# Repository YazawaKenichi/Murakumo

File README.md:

# Murakumo

```
* 8b    d8 88   88 88""Yb    db    88  dP 88   88 8b    d8  dP"Yb             Yb    dP 888888 *
* 88b  d88 88   88 88__dP   dPYb   88odP  88   88 88b  d88 dP   Yb             Yb  dP  88oo." *
* 88YbdP88 Y8   8P 88"Yb   dP__Yb  88"Yb  Y8   8P 88YbdP88 Yb   dP              YbdP      `8b *
* 88 YY 88 `YbodP' 88  Yb dP""""Yb 88  Yb `YbodP' 88 YY 88  YbodP  oooooooooo    YP    8888P' *
```

Yazawa の初めてのロボトレの情報を置いておくリポジトリ。
##### Excel フォルダ
機体の仕様決定

##### Inventor フォルダ
具体的な機体のグラフィック

##### Circuit フォルダ
KiCAD データとガーバーデータ

##### Program フォルダ（未作成）
実行プログラムや試行錯誤したプログラム

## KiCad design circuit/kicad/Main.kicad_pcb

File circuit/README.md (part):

回路設計時のノート

いろいろ悩みそうなところだけど、どこから悩めばいいのかもわからなかったので、まずはモータドライバ回路から設計しようと思う。

モータドライバ設計の前に、H ブリッジを駆動するためのゲートドライバ選びについて記述する。
##### ゲートドライバ
まず、ゲートドライバに必要な要素は以下の通り。
- Nch フルブリッジ回路を組むことができるか？
- 100% duty で出力できるか？
ということらしい。

PWM 周波数の話。
PWM 周波数は小さすぎるとトルクが足りなくなり、大きすぎるとモータによるサージの影響を受けやすくなる。よって適度な周波数に決める必要がある。

###### Nch フルブリッジ回路
Nch フルブリッジ回路を組むことの利点は以下。
- Pch は Nch に比べて性能が低い。
- Pch は品種があまりない。
- パワー素子は一種類のみで済ませて手間を省きたい。（Pch か Nch にそろえて同じ素子を使って製作できるようにしたい。）
- Pch は値段が高い。
上記理由を先輩に教えていただいたが、教えていただいた後にネットを探したところ、同様の記述を発見した。[参考](http://blog.livedoor.jp/wata_net/archives/2147292.html)。
[こっちのサイト](https://qiita.com/panzakii/items/97eca16954d34ecf0c8b)には「なぜフルNchにこだわるかというと、単純にその方が流せる電流が大きくなるからです。実はPchFETはNchFETに比べ流せる電流が少ないのです。原理について説明しだすと本当にキリがないので説明しません。興味のある人はググってください。」などと記述されているが、ググってもそんな記述は一切出てこない。なんなんだ。

「品種が多いから Pch よりも大電流の流せる Nch MOSFET」ならわかるが、「原理」とか「説明しだすとキリがない」とか記述されているのは本当に意味が分からない。

###### 100% duty で出力
- 最大出力で出せたほうが良いにきまっとるやろ！

二つのメリットをカバーできて、より入手しやすい IC が A3921 だそうで、それが理由でよく利用される。

##### モータドライバ
ゲートドライバが決まったところで、次に使用する FET とそれにつながる制限抵抗やコンデンサの値を決める必要がある。
特にこの抵抗とコンデンサは真剣に決めないとショートしてリポが死ぬ。マジで。
モータに入る電流は最大でも 4.34A なので、この許容電流に耐えうるケーブルは AWG22 になる。（AWG23 がいい感じに 4.7A の許容電流なのだが、9号館にないのでしょうがない。）
この AWG23 を圧着できるコネクタが XA コネクタなので、モータの電流が通るところのコネクタはすべて XA にしようと思う。
電源コネクタと電源回路をモータドライバ回路の方に設置することで、わざわざマイコン側から電力をモータドライバ回路に送る必要を無くす。

***書き途中***

DRV8874 のデータシートを読んで得た情報
- CPH CPL 間に 22nF のコンデンサ
- nFault は故障で LOW nSleep は LOW でスリープ => nFault と nSleep を直結すると故障と同時にスリープに入る。
- nFault には外部プルアップが必要。

SR ピンは 1 にすると FET 経由で回生する

SR ピンを 0 にするとダイオード経由で回生する

Figure 2: Fast Decay Power Bridge Current Paths が一番創造に近いモータドライバの制御に近い

PWMH PWML には常に 1 を入れて、PHASE に 

##### CPU
先輩が STM32F405RGT6 を束買いしているので、とりあえずこれにするのはアリ。
クロック数とメモリと機能的に、ロボトレにいい塩梅で使えそうなのがこの CPU らしい。

***書き途中***

##### 電源回路
この電源回路を決めるのにレギュレータを選ぶ必要があるのだが、レギュレータの出力が決まらない以上は手の付けようがない。だからさっさとほかの回路作れ。電源選びは最後だ。
=======
回路設計時のノート

いろいろ悩みそうなところだけど、どこから悩めばいいのかもわからなかったので、まずはモータドライバ回路から設計しようと思う。

使いたいモータがある -> 必要な電流量に耐える FET -> それを駆動できるゲートドライバを探す<br>
使いたいセンサがある -> 

モータドライバ設計の前に、H ブリッジを駆動するためのゲートドライバ選びについて記述する。
##### ゲートドライバ
まず、ゲートドライバに必要な要素は以下の通り。
- Nch フルブリッジ回路を組むことができるか？
- 100% duty で出力できるか？
ということらしい。

###### Nch フルブリッジ回路
Nch フルブリッジ回路を組むことの利点は以下。
- Pch は Nch に比べて性能が低い。
- Pch は品種があまりない。
- パワー素子は一種類のみで済ませて手間を省きたい。（Pch か Nch にそろえて同じ素子を使って製作できるようにしたい。）
- Pch は値段が高い。
上記理由を先輩に教えていただいたが、教えていただいた後にネットを探したところ、同様の記述を発見した。[参考](http://blog.livedoor.jp/wata_net/archives/2147292.html)。
[こっちのサイト](https://qiita.com/panzakii/items/97eca16954d34ecf0c8b)には「なぜフルNchにこだわるかというと、単純にその方が流せる電流が大きくなるからです。実はPchFETはNchFETに比べ流せる電流が少ないのです。原理について説明しだすと本当にキリがないので説明しません。興味のある人はググってください。」などと記述されているが、ググってもそんな記述は一切出てこない。なんなんだ。

「品種が多いから Pch よりも大電流の流せる Nch MOSFET」ならわかるが、「原理」とか「説明しだすとキリがない」とか記述されているのは本当に意味が分からない。

###### 100% duty で出力
- 最大出力で出せたほうが良いにきまっとるやろ！
100% duty で出せるかどうかってどうやって決まるんだろう...

二つのメリットをカバーできて、より入手しやすい IC が A3921 だそうで、それが理由でよく利用される。
A3921 の仕様
ゲート電圧は基準電位から +15V 以内の範囲が出力される様子。具体的には、ハイサイド出力が SA の電位よりも 0 ~ 15V 高くなり、ローサイド出力が GND 電位よりも -5 ~ 16V 高くなるように出力される。

A3921 のデータシートを読んで得た情報
- GHA and GHB Pins
- ゲート抵抗はできるだけ FET に近いところに置く必要がある。（なんでや）
- ＞ そもそもゲート抵抗をつける理由として
- ＞＞ FET 内部のコンデンサ成分と、導線自体によるインダクタンス成分が共振し、それに影響して FET やマイコンが破損する恐れがある。
- ＞＞ ドレイン電圧の立ち上がりと立下りが早すぎてノイズへの影響が大きくなる。
- ＞＞ ゲート電流が大きすぎて FET 前段の制御回路が破損する。
- ＞ この中で FET と抵抗の距離と関係がありそうな理由としては「導線自体のインダクタンス」だろう。抵抗からFETまでの導線の長さを小さくする、すなわちインダクタンスを小さくすることでノイズを軽減するといったところか。
- いまいちよくわからないところが、「GHx going low turns on the lower half of the drive, sinking current from the external FET gate circuit to the corresponding Sx pin, turning off the FET.」の一文で、GHx を Low にしたらドライブの下半分が ON になる？ってどういうことだ？
- Bootstrap Capacitor Selection
- ブートストラップコンデンサ CBOOTx は、正しく選択する必要がある。
- コンデンサの静電容量が大きいと、コンデンサの充電に時間が浪費され、結果として最大デューティーサイクルと PWM 周波数の制限が小さくなってしまう。
- 逆に小さいと、Charge Sharing によって、電荷が CBOOTx から FET ゲートに転送されるときに大きな電圧降下が発生する可能性があるらしい。
- ＞ Charge Sharing ってなんだ？
- ＞＞ 英語版 Wiki によると、Charge Sharing は、ある電子ドメインからほかの電子ドメインへの電荷の移動による信号劣化の影響。らしい。は？
- ＞ よくわからないけど、とにかく電荷を共有して、出力電圧レベルが退化したり、誤った出力値が発生したりする可能性があるっぽい。
- この電圧降下を小さくするために、CBOOTx の電荷 QBOOT は、FET のゲート QGATE に必要な電荷よりもはるかに大きくする必要がある。その"はるかに大きい"というのは、20 倍だそうだ。
- QBOOT というのは、CBOOTx に蓄えられる電気量なので、CBOOT * VBOOT で求めることができる。そして上記より、これは QGATE の 20 である必要があるので、ブートストラップに接続するコンデンサの、適切な電気容量 CBOOT を求める式は、以下のようになる。
- CBOOT = QGATE * 20 / VBOOT
- 係数 20 を選択した場合、FET が ON の時の VBOOT と OFF の時の VBOOT の差は約 5% だそう。通常動作条件下での VBOOT の最大電圧は VREG らしい。
- ＞ VREG の値について。。。疑問がある。
- ＞＞ Terminal List には Regulated 13V と説明があるのに、
- VBB 電源が 16V より大きいとき、レギュレータは単純なリニアレギュレータとなる。16V 未満では、安定したレギュレートをするために、ポンプコンデンサ CP が必要。
- このコンデンサ CP の最小値は 220nF である必要があり、通常は 470nF を接続する。
- 安定してレギュレートされた 13V は VREG 端子で使用できる。ローサイドドライブとブートストラップコンデンサに過渡充電電流を供給するために十分大きなストレージコンデンサを接続する必要がある。
参考になったサイト
- ハイサイド Nch MOSFET の話やブートストラップ回りについては[このサイト](https://techweb.rohm.co.jp/knowledge/dcdc/dcdc_sr/dcdc_sr01/829)が参考になった。

###### duty rate
[このサイト](https://sgrsn1711.hatenablog.com/entry/2019/04/29/152425)が参考になった。<br>
PWM 制御は PWM パルス波を用いて電圧を制御する方法。しかし **『PWM のデューティー比を線形に動かしても電圧は線形』にならない。** <br>
具体的な式は (実効値) = (最大瞬時値) * √(デューティー比)<br>
最大瞬時値：パルス波が HIGH の時の電圧<br>
デューティー比：そのままの意味（但し 0 以上 1 以下）<br>
実効値：PWM の電圧・電流をこれと同じ働きをする直流の電圧・電流の大きさに置き換えて表した値<br>
両辺を二乗して両辺を (モータの抵抗) で割ると<br>
(実効電圧) / (モータの抵抗) = (デューティー比) * (最大瞬時電圧) / (モータの抵抗)<br>
すなわち<br>
(実効電力) = (デューティー比) * (ドライバの電力)<br>
となり、**(デューティー比) は 電力 の比例定数となっている**ことがわかる。<br>
<br>
[このサイト](https://detail-infomation.com/gate-driver-type/)によると、ターンオンを速くする回路よりもターンオフを速くする回路の方が頻繁に用いられるらしい。たしかに、4月に制作したミニトレーサ回路も、ターンオフが速くなる方向にダイオードが設けられていた。ターンオフ抵抗が小さいので、MOSFET のミラー容量を介して誤ターンオンを防ぐことができるようだ。

##### モータドライバ
ゲートドライバが決まったところで、次に使用する FET とそれにつながる制限抵抗やコンデンサの値を決める必要がある。
特にこの抵抗とコンデンサは真剣に決めないとショートしてリポが死ぬ。マジで。

参考までに先輩のデータを置いておく。
DRV8874 (野村先輩)
DRV8873 + INA260 (井口先輩青機体)
DRV8701 + AON7xxx (井口先輩紫機体)
A3921 + IRF8915 (下鳥先輩 VCM 機体)

H ブリッジが組める IC を Digi-Key で探したが、どうやら今は在庫切れっぽい。は？どうすりゃいいの？
- パターン１：ほかのサイトでも探してみる
- パターン２：H ブリッジを自作する
- パターン３：何？

Digi-Key で在庫を無視して H ブリッジを絞り込んで、当然というか、上記の通り在庫がないので Mouser で検索していく。
- [L9958](https://www.mouser.jp/ProductDetail/STMicroelectronics/L9958?qs=mxm%2FV7p14IPZ8VUmCRyJ0Q%3D%3D) が良さそう。電圧と必要な電流で絞り込んだら L9958 うんたら～みたいなのがたくさん出てきたが、データシートは同じものだったので、データシートを読む分にはどれを選んでも大丈夫そう。電流制限機能があり、CL ピンに設定する H/L でその閾値を決めているようだ。実際に通す電流は 5A 行かないくらいなので、制限 8A で十分である。L9958 うんたら～を絞るのはどうすればよいのだろう... 何が違うのかをデータシートから読む必要がありそう。また、消費電力を計算してこの IC で良いかも吟味した方がよい。

Digi-Key で H ブリッジを検索してそれを別のショップで調べてみる。そうすればほしい IC が Digi-Key の在庫に左右されずに使用できる。
試しに H ブリッジを Digi-Key で用途とパッケージで絞り込んで調べたところ、[このような一覧](https://docs.google.com/spreadsheets/d/1YwifbfS08Ro-1kxqgMN1l2ujk6fK_v7bKf-RipdZybw/edit?usp=sharing)が吐き出された。
- DRV8874 (野村先輩が使用している IC と同じもの)
- DRV8848
- DRV8220
さらに、このうち欲しい電流が吐き出せるのが [DRV8874 (野村先輩と同じ IC)] が選出される。<br>
ただ、この DRV8874 なのだが、Digi-Key, Mouser, RS Components, Akizuki, Marutsu のどれで調べても在庫切れ。もうダメじゃん...<br>
野村先輩の在庫と、評価ボードからパクればヨシッ！<br>

QFP と QFN
QFP はよく見る足が外に出たパッケージ、QFN は足が出てないパッケージ。リフローでしかつけられない奴が QFN 一応 9 号館でリフローできるらしい。
QFN にすればサイズ縮小できるし、条件に合った IC も見つかりやすいから良いんだけど、リフローする IC は一気にリフローする必要があるから、燃えたところだけ直すとかそういうことがやりにくい。
初めてなんだから回路は修正しやすいほうが良い。絶対 QFP がいいやろ。

DRV8874 データシート 7.3.1 に推奨抵抗値が書いてある。
IPROPI に発生する電流は以下の式で与えられる。
Iipropi = (ILS1 + ILS2) * Aipropi
ILS はローサイド FET のドレイン電流。Aipropi は比例定数。おおよそ 450uA/A とされている。
モータを通す最大電流は 4.34A なので、最大の Iipropi は 1.953mA となる。ここに抵抗と ADC を繋ぐことでマイコンで処理することができるようになる。（抵抗が電流を電圧に変換するための抵抗になる。）
***途中略***
Vref の抵抗値は 33k, 33k で良い気がしてきた。（合計 66k ohm になるように選定。）結局 Itrip の値は Ripropi の値で決めればいいと思う。

###### Power MOSFET<br>
FET の耐圧（D-S 間電圧）と流したいドレイン電流（ID 電流）で大体の規格が絞れる。<br>
そこから、[ON 抵抗](https://www.rohm.co.jp/electronics-basics/transistors/tr_what9)と[スイッチング速度]()から、損失の大きさを計算してそれに耐えるものを選ぶ。<br>
DCX 10L 公称 4.5V の起動電流 1.55A で、これに 12V をかける。その時の電流値を考えて使う必要がある。<br>
- 別ディレクトリの Excel データによると ID = 3.06A (2S (8.9V)), 4.34A (3S (12.6V)) であることが算出された。3S 使うことも考えて、4.34A に耐えるものを選ぶようにすればよさそう。<br>
ついでに、配線幅については、右モータと左モータでひとつづつ使うことも考慮して設計する必要がある。よって上記条件によって 4.34mm 以上の配線幅となっていればよいことになる。<br>
- ON 抵抗については、パッケージが小さい方が ON 抵抗が大きく、パッケージが小さいと ON 抵抗が大きくなる。<br>
- 今回作る基板はサイズが比較的大きく、パッケージの違いによる大きさの違いは考慮しなくて良いと思う。よって ON 抵抗のより小さいものを選んでおけば良い。<br>
- [スイッチング速度についてはこのサイトが強そう](https://xtech.nikkei.com/atcl/learning/lecture/19/00080/00002/)<br>
digikey で以下の条件で絞り込んだ<br>
- Nch フルブリッジを内蔵したトランジスタアレイ IC<br>
- 部品状況：アクティブ<br>
- FET タイプ：N チャンネル 4 個 (H ブリッジ)<br>
- Vdss：24V 以上 (上条件適応後だと 30V 以上)<br>
- Id：9A 以上 (上条件適応後だと 13A 以上)<br>
- 取り付けタイプ：面実装<br>
以上の条件だとただ一つ [DMHT3006LFJ](https://www.diodes.com/assets/Datasheets/DMHT3006LFJ.pdf) のみに絞られた。<br>
トランジスタシングルの場合で絞り込んでみたい。<br>
FET で H ブリッジを組むことを考えてみる。<br>
絞り込み条件<br>
- Transistor - FET, MOSFET - Array<br>
- 部品状況 : Active<br>
- FET type : 2Nch (dual) | Nch \*2 (Half Bridge)<br>
- FET method : Logic Level Gate<br>
まずは上記で絞り込み、下記を追加<br>
- Vdss : 20V (大きすぎるとオン抵抗が大きくなる傾向がある。）<br>
- Id : 5A | 20A | 40A<br>
次に以上で絞り込み、「オン抵抗は小さいと電力が小さく済む」「ゲート電荷が小さいほうがスイッチング時のロスが減る（高速スイッチングができる）」「オン抵抗とゲート電荷はトレードオフ」という知識を以って、下記をさらに追加<br>
- <br>
モータの PWM 制御において「高速スイッチングができる」というのは大したメリットではないような気がした。なので「オン抵抗かゲート電荷か」については「オン抵抗」の方を取ることにする。<br>
因みに「チップサイズが大きい => オン抵抗が小さい => ゲート電荷が大きい」と、チップサイズとも関係がある様子。ただシャーシ基板だし、サイズはまだ考慮しなくていい気がする。<br>
「MOSFET の寄生容量・入力容量・出力容量・帰還容量 の関係」で一つ記事が書けるくらいの内容がある。（俺が俺に向けて知っておいてほしいことの一つ）<br>
このうちの 入力容量 が ゲート電荷 と直接的に関係があるもの。よって、ゲート電荷の大小を考えることは入力容量の大小を考えることと同じである。<br>
MOUSER で FET を調べてみる。<br>
- MOSFET SMD/SMT N-Channel MOSFET
- Rds On で昇順ソートして 2 ページまで CSV で吐き出す。
- Rds On が一番小さいのが [PSMN1R5-30BLEJ](https://www.mouser.jp/ProductDetail/Nexperia/PSMN1R5-30BLEJ?qs=1sbE9T7hb3ZypDkHrUdzRQ%3D%3D&utm_source=mouser-refine-download&utm_medium=file&utm_campaign=PSMN1R5-30BLEJ&utm_content=Nexperia) だった。ただ在庫が 5 しかあらん。
- 次に小さいのが [PSMN1R5-25YL,115](https://www.mouser.jp/ProductDetail/Nexperia/PSMN1R5-25YL115?qs=HnaUIVfgVjDTvZFUMaRG6Q%3D%3D&utm_source=mouser-refine-download&utm_medium=file&utm_campaign=PSMN1R5-25YL%2C115&utm_content=Nexperia) になった。こっちは在庫が 50 くらいある。これで良いんじゃね？いったんこれで考えてみる。
- 

***書き途中***

##### ラインセンサ
- 野村先輩によると、アナログ値を返すセンサと、ディジタル値を返すセンサの二種類がある。
- 試しに digikey で調べてみようとしたところ、『光センサ - フォトインタラプタ - スロットタイプ - トランジスタ出力』『光センサ - フォトインタラプタ - スロットタイプ - ロジック出力』という分類があり、トランジスタ出力が一般的なアナログ値を返すフォトインタラプタで、ロジック出力が野村先輩が言っていたディジタル値を返すセンサなのだろう。
- 接続する抵抗によって閾値を変更する。
- [なんかいい感じのサイト見つけた](https://components.omron.com/jp-ja/products/basic-knowledge/sensors/photomicro-sensors/technology)
- [こっちはフォトセンサの設計についてのサイト](https://toshiba-semicon-storage.com/content/dam/toshiba-ss/jp/docs/design-support/elearning/elearning_discrete05_r51.pdf)
勝手な予想混じりではあるが、メリットとデメリットについて考えてみる。<br>
アナログ出力のメリット<br>
- 環境が変わってもプログラム上で閾値を変更すればいいだけ<br>
アナログ出力のデメリット<br>
- ソースコードが長くなる
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
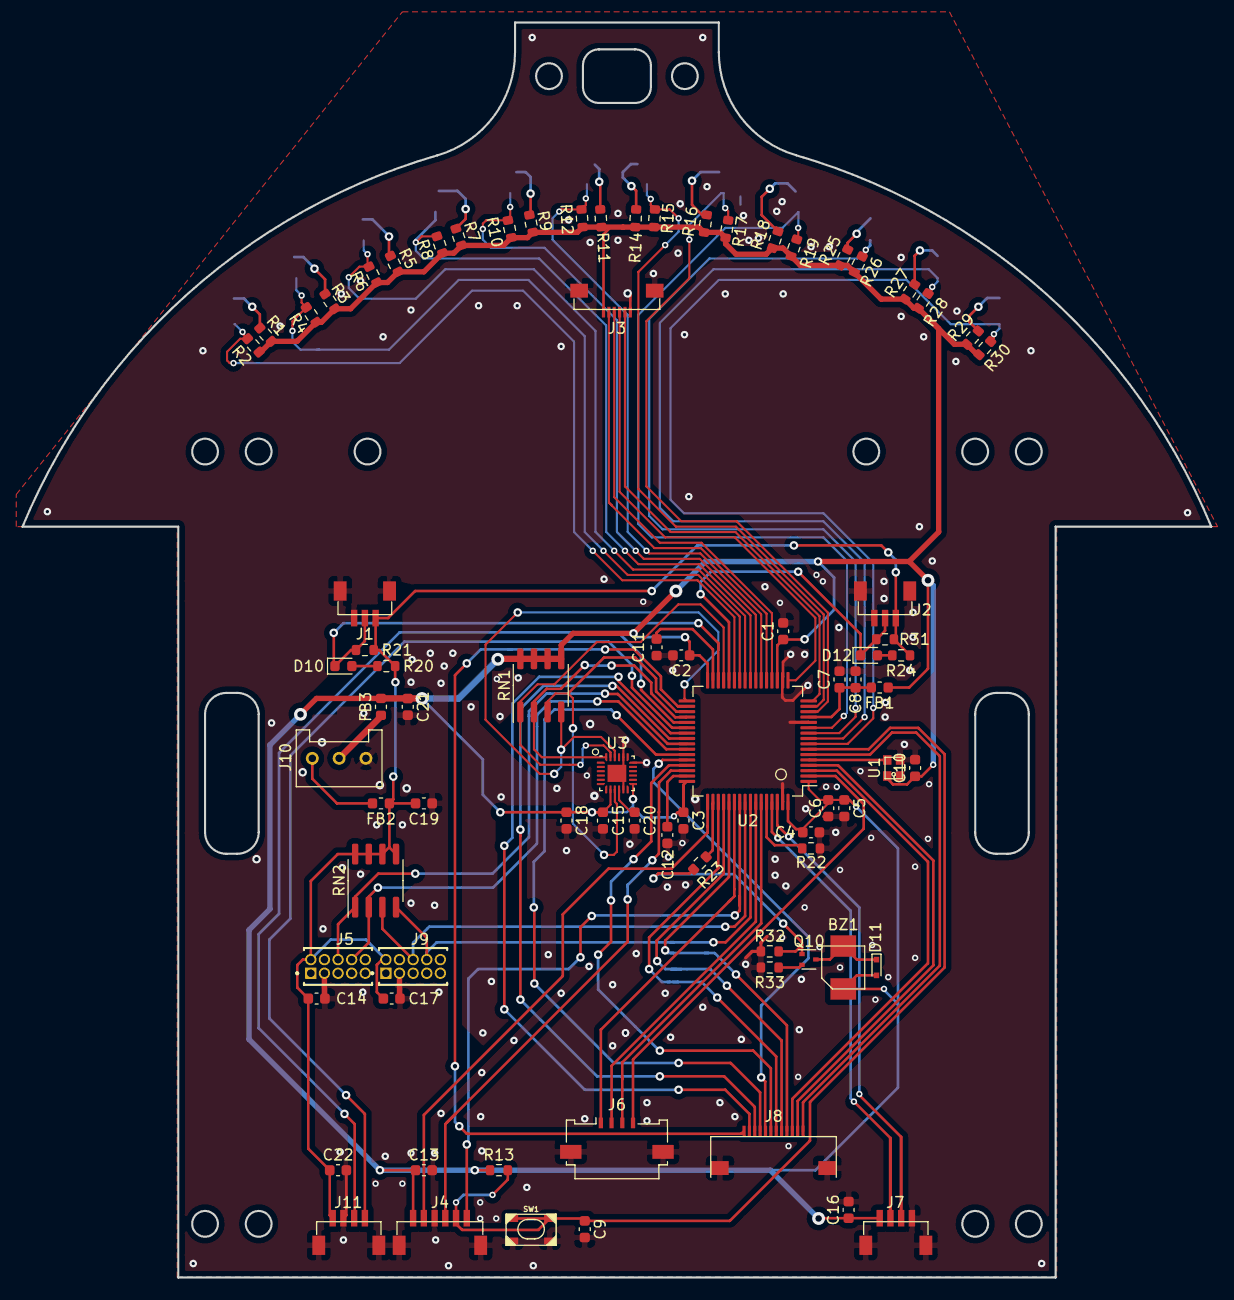
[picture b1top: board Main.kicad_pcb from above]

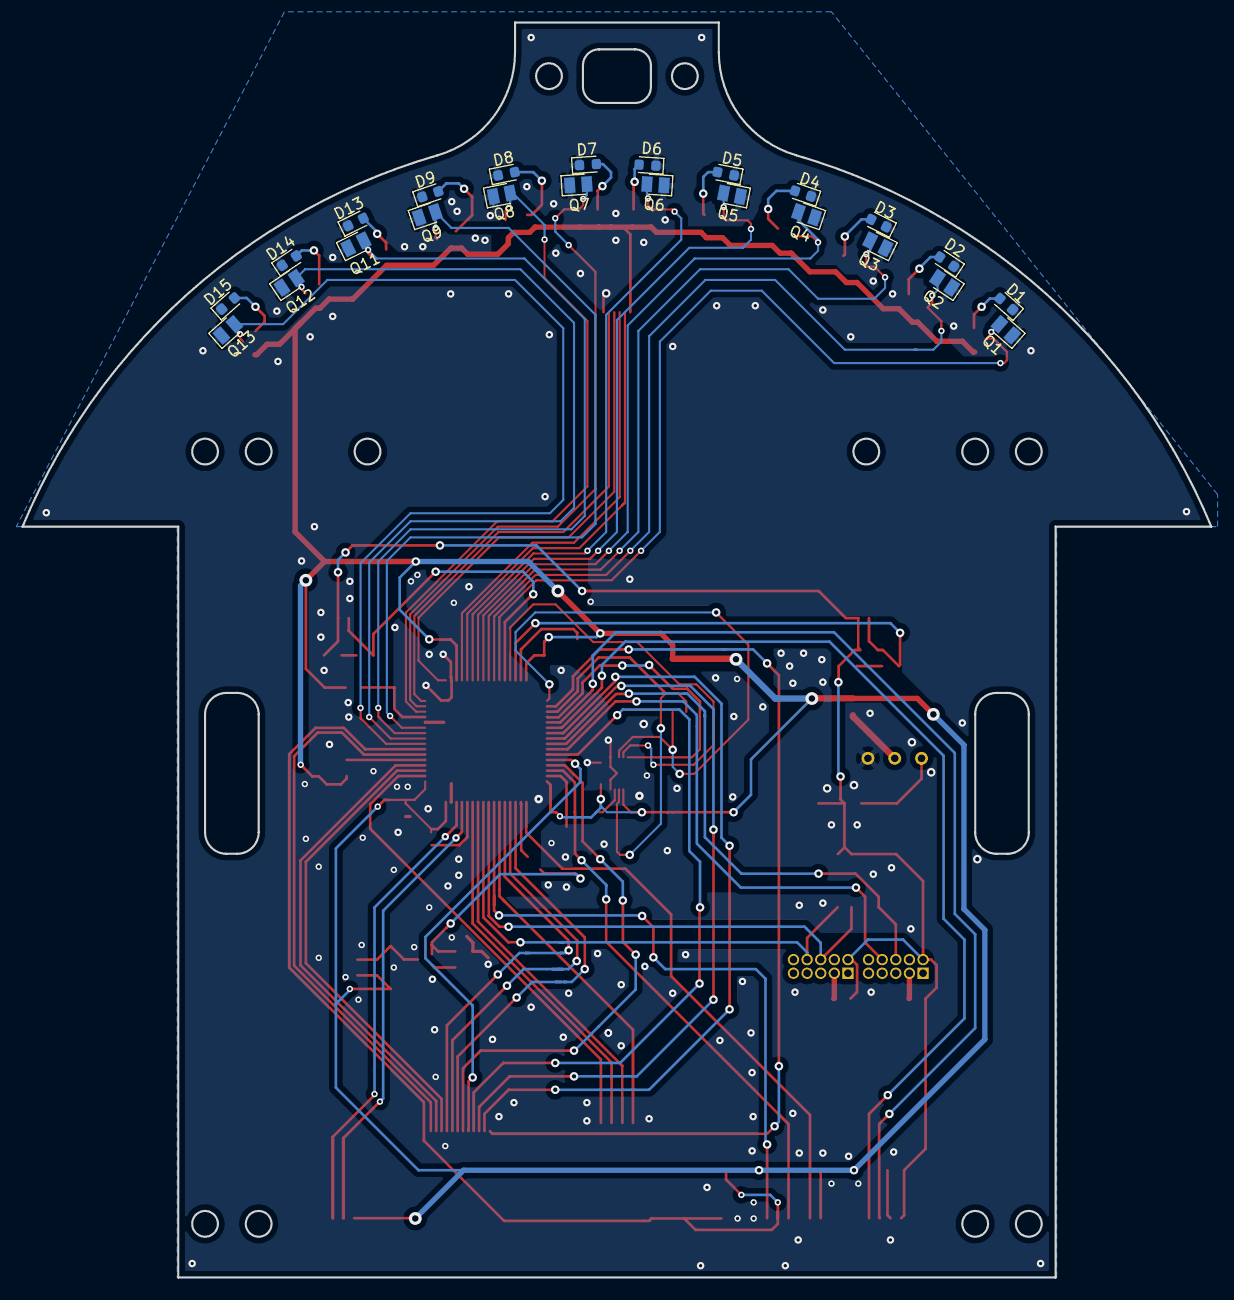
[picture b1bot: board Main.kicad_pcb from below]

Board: 2 copper layers, 110.8 x 117.0 mm, 104 parts (24 on the bottom side), 79 nets.

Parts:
BZ1: TE044003-4
C1, C2, C3, C4, C6, C7, C9, C10, C13, C14, C15, C16, C17, C18, C19, C20, C21, C22: 0.1u; C_0603_1608Metric
C5: 4.7u; C_0603_1608Metric
C8: 1u; C_0603_1608Metric
C11, C12: 2.2u; C_0603_1608Metric
D1, D2, D3, D4, D5, D6, D7, D8, D9, D13, D14, D15: SIR19-21C/TR8; D_0603_1608Metric
D10, D12: SMLEN3WBC8W1; D_0603_1608Metric
D11: RB751S40-AU_R1_000A1; SOD-523
FB1, FB2, FB3: 470; L_0603_1608Metric
J1, J2: SH3; SH_01x03
J3: FFC6; Molex_0545480671_01x06_P0.5mm
J4: SH6; SH_01x06
J5, J9: FTSH2x5; SAMTEC_FTSH-105-01-L-D-K
J6: FFC4; Molex_200528-0040_1x04-1MP_P1.00mm_Horizontal
J7, J11: SH4; SH_01x04
J8: FFC12; WürthElektronik_687112183722_01x12_P0.5mm
J10: PA3; PA_01x03
Q1, Q2, Q3, Q4, Q5, Q6, Q7, Q8, Q9, Q11, Q12, Q13: TEMT7100X01
Q10: 2N7002T; SOT-523
R1, R3, R5, R7, R9, R11, R14, R16, R18, R23, R25, R27, R29: 100; R_0603_1608Metric
R2, R4, R6, R8, R10, R12, R13, R15, R17, R19, R21, R22, R26, R28, R30, R31, R32: 10k; R_0603_1608Metric
R20, R24: 470; R_0603_1608Metric
R33: 36; R_0603_1608Metric
RN1, RN2: 10k; SOIC-8_3.9x4.9mm_P1.27mm
SW1: SKRPABE010
U1: ASTMLPA-16MHz-LJ-E-T; ASTMLPA-16.000MHz-LJ-E-T
U2: STM32F405RGTx; LQFP-64_10x10mm_P0.5mm
U3: ICM-20648; QFN-24-1EP_3x3mm_P0.4mm_EP1.75x1.6mm

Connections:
+3V3: BZ1.1, C1.1, C2.1, C3.1, C4.1, C5.1, C6.1, C10.1, C13.1, C15.1, C16.1, C18.1, C21.1, D11.1, FB1.1, FB3.2, J3.6, J4.1, J7.1, R1.1, R2.1, R3.1, R4.1, R5.1, R6.1, R7.1, R8.1, R9.1, R10.1, R11.1, R12.1, R13.1, R14.1, R15.1, R16.1, R17.1, R18.1, R19.1, R25.1, R26.1, R27.1, R28.1, R29.1, R30.1, RN1.5, RN1.6, RN1.7, RN1.8, U1.4, U2.1, U2.19, U2.32, U2.48, U2.64, U3.8, U3.13
+5V: C14.1, C17.1, C19.1, C22.1, FB2.2, J1.1, J2.1, J5.2, J9.2, J11.1, R20.1, R21.1, R24.1, R31.1, RN2.5, RN2.6, RN2.7, RN2.8
/DRV1_EN: J6.2, U2.58
/DRV1_PN: J6.1, U2.54
/DRV2_EN: J6.3, U2.59
/DRV2_PN: J6.4, U2.2
/LED_B: J8.3, U2.40
/LED_G: J8.4, U2.43
/LED_R: J8.5, U2.44
/LED_Red: J8.1, U2.34
/LED_White: J8.2, U2.39
/Rotary1: J8.9, U2.53
/Rotary2: J8.7, U2.51
/Rotary4: J8.6, U2.45
/Rotary8: J8.8, U2.52
/SW1: J8.10, U2.3
/SW2: J8.11, U2.4
/SW3: J8.12, U2.6
/Sensor01: Q1.1, R2.2, U2.27
/Sensor02: Q2.1, R4.2, U2.26
/Sensor03: Q3.1, R6.2, U2.25
/Sensor04: Q4.1, R8.2, U2.24
/Sensor05: Q5.1, R10.2, U2.23
/Sensor06: Q6.1, R12.2, U2.22
/Sensor07: Q7.1, R15.2, U2.15
/Sensor08: Q8.1, R17.2, U2.14
/Sensor09: Q9.1, R19.2, U2.11
/Sensor10: Q11.1, R26.2, U2.10
/Sensor11: Q12.1, R28.2, U2.9
/Sensor12: Q13.1, R30.2, U2.8
Encorder1_A: J5.6, RN2.1, U2.41
Encorder1_B: J5.8, RN2.2, U2.42
Encorder2_A: J9.6, RN2.3, U2.56
Encorder2_B: J9.8, RN2.4, U2.57
GND: C1.2, C2.2, C3.2, C4.2, C5.2, C6.2, C7.2, C8.2, C9.2, C10.2, C11.2, C12.2, C13.2, C14.2, C15.2, C16.2, C17.2, C18.2, C19.2, C20.2, C21.2, C22.2, D1.1, D2.1, D3.1, D4.1, D5.1, D6.1, D7.1, D8.1, D9.1, D13.1, D14.1, D15.1, J1.3, J2.3, J3.1, J4.3, J5.3, J7.4, J9.3, J10.3, J11.2, Q1.2, Q2.2, Q3.2, Q4.2, Q5.2, Q6.2, Q7.2, Q8.2, Q9.2, Q11.2, Q12.2, Q13.2, R22.2, R32.1, R33.1, SW1.2, U1.2, U2.12, U2.18, U2.63, U3.11, U3.18, U3.20
I2C_SCL: J7.2, U2.61
I2C_SDA: J7.3, U2.62
ICM_MISO: RN1.3, U2.35, U3.9
ICM_MOSI: RN1.2, U2.36, U3.24
ICM_SCLK: RN1.1, U2.29, U3.23
ICM_nCS: RN1.4, U2.33, U3.22
unnamed: BZ1.2, D11.2, Q10.3
unnamed: C7.1, C8.1, FB1.2, U2.13
unnamed: C11.1, U2.31
unnamed: C12.1, U2.47
unnamed: C20.1, U3.10
unnamed: D1.2, R1.2
unnamed: D2.2, R3.2
unnamed: D3.2, R5.2
unnamed: D4.2, R7.2
unnamed: D5.2, R9.2
unnamed: D6.2, R11.2
unnamed: D7.2, R14.2
unnamed: D8.2, R16.2
unnamed: D9.2, R18.2
unnamed: D10.2, R20.2
unnamed: D12.2, R24.2
unnamed: D13.2, R25.2
unnamed: D14.2, R27.2
unnamed: D15.2, R29.2
unnamed: FB2.1, J10.1
unnamed: FB3.1, J10.2
unnamed: J3.2, U2.16
unnamed: J3.3, U2.17
unnamed: J3.4, U2.20
unnamed: J3.5, U2.21
unnamed: Q10.1, R23.1, R32.2
unnamed: Q10.2, R33.2
unnamed: R22.1, U2.60
unnamed: R23.2, U2.50
unnamed: U1.3, U2.5
SWCLK: J4.2, U2.49
SWDIO: J4.4, U2.46
SWO: J4.6, U2.55
SubSens1: D12.1, J2.2, R31.2, U2.28
SubSens2: D10.1, J1.2, R21.2, U2.30
USART_RX: J11.4, U2.38
USART_TX: J11.3, U2.37
nRST: C9.1, J4.5, R13.2, SW1.1, U2.7

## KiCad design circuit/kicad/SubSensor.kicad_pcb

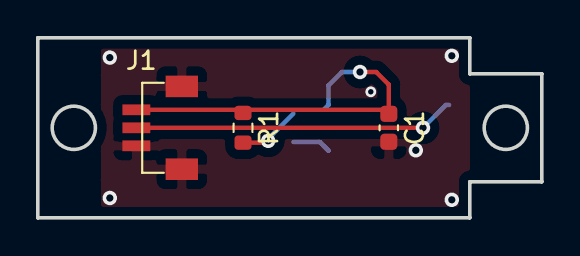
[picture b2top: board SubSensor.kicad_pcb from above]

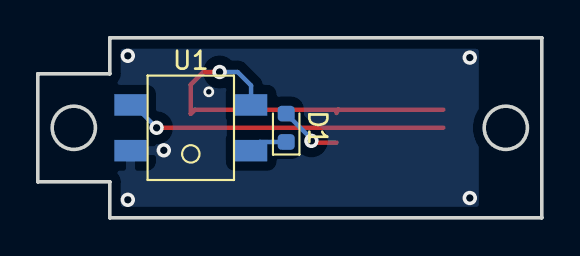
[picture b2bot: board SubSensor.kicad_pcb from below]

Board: 2 copper layers, 28.0 x 10.0 mm, 5 parts (2 on the bottom side), 5 nets.

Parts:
C1: 0.1u; C_0603_1608Metric
D1: SIR19-21C/TR8; D_0603_1608Metric
J1: SH3; SH_01x03
R1: 68; R_0603_1608Metric
U1: S7136

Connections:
+5V: C1.1, J1.3, R1.1, U1.2
GND: C1.2, J1.1, J1.MP, U1.4
unnamed: D1.1, U1.1
unnamed: D1.2, R1.2
unnamed: J1.2, U1.3

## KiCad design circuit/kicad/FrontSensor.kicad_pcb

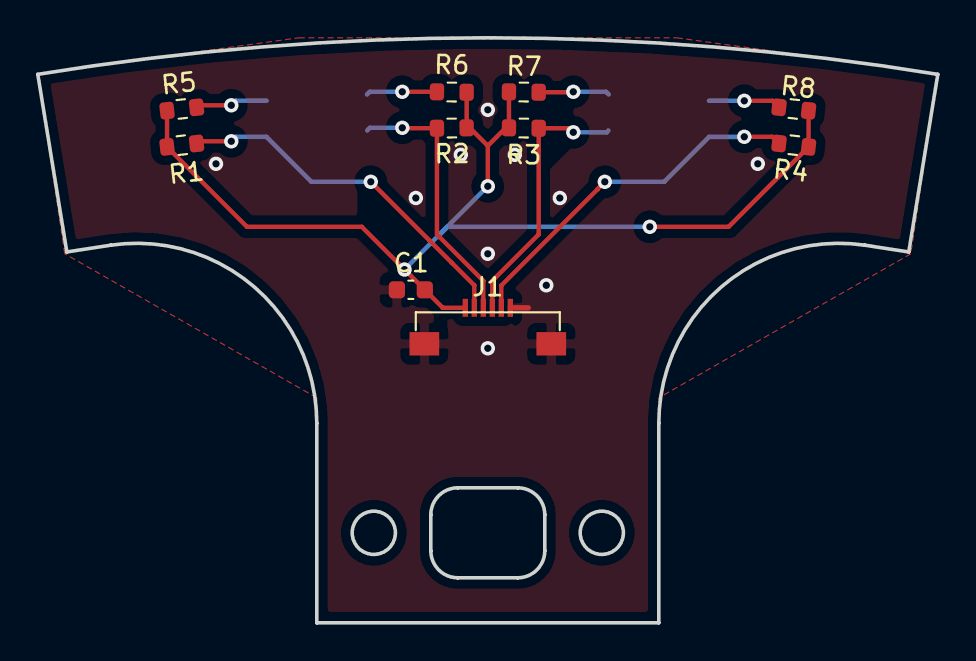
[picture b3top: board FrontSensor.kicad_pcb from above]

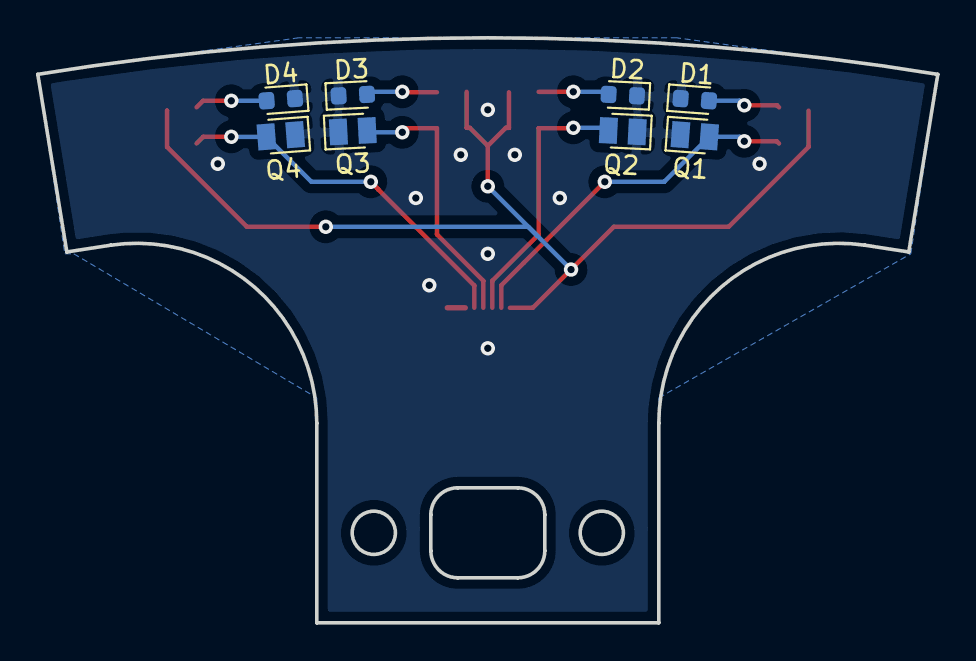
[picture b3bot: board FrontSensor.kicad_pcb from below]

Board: 2 copper layers, 50.0 x 32.5 mm, 18 parts (8 on the bottom side), 10 nets.

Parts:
C1: 0.1u; C_0603_1608Metric
D1, D2, D3, D4: SIR19-21C/TR8; D_0603_1608Metric
J1: FFC6; Molex_0545480671_01x06_P0.5mm
Q1, Q2, Q3, Q4: TEMT7100X01
R1, R2, R3, R4: 10k; R_0603_1608Metric
R5, R6, R7, R8: 100; R_0603_1608Metric

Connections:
+3V3: C1.1, J1.1, R1.1, R2.1, R3.1, R4.1, R5.1, R6.1, R7.1, R8.1
GND: C1.2, D1.1, D2.1, D3.1, D4.1, J1.6, J1.MP, Q1.2, Q2.2, Q3.2, Q4.2
unnamed: D1.2, R5.2
unnamed: D2.2, R6.2
unnamed: D3.2, R7.2
unnamed: D4.2, R8.2
unnamed: J1.2, Q1.1, R1.2
unnamed: J1.3, Q2.1, R2.2
unnamed: J1.4, Q3.1, R3.2
unnamed: J1.5, Q4.1, R4.2

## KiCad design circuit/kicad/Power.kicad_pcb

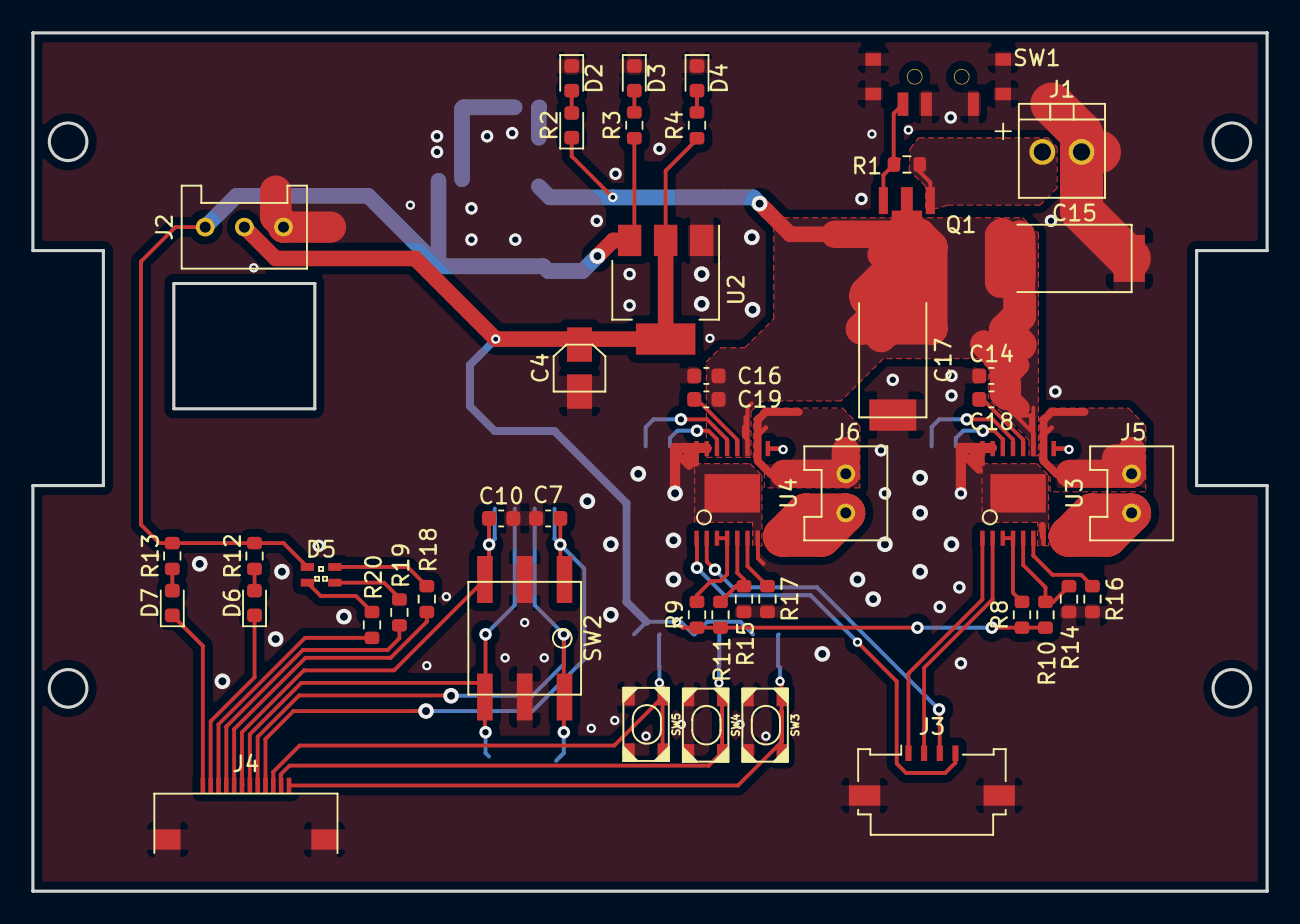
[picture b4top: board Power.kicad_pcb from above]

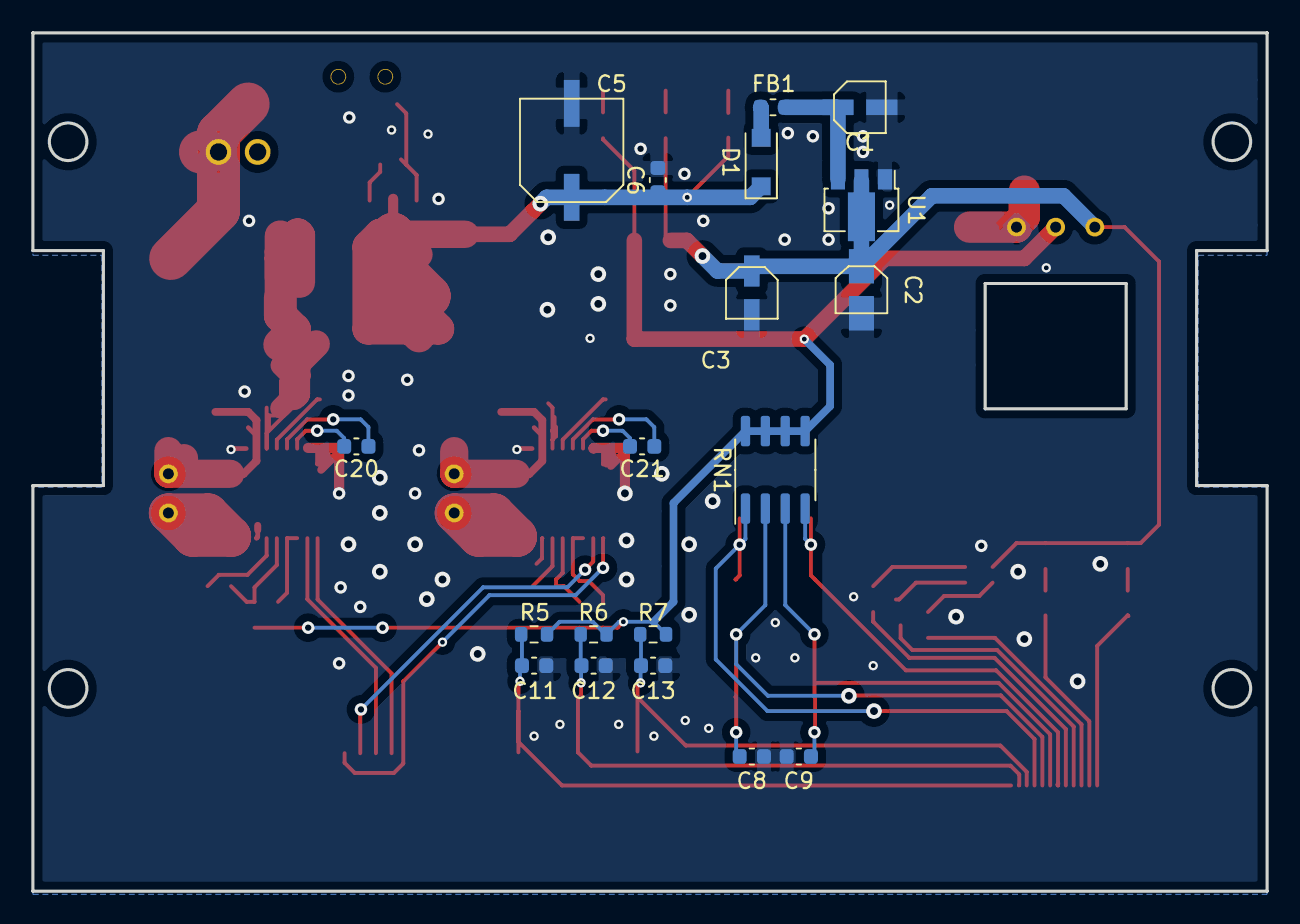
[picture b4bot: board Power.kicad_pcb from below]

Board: 2 copper layers, 78.8 x 54.8 mm, 66 parts (19 on the bottom side), 48 nets.

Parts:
C1, C3: 10u; AVE106M16A12T-F
C2, C4: 22u; 865090168010
C5: 220u; EEE-1AA221XP
C6, C7, C8, C9, C10, C11, C12, C13, C14, C16, C18, C19: 0.1u; C_0603_1608Metric
C15, C17: 100u; ECASD91B107M012K00
C20, C21: 22n; C_0603_1608Metric
D1: SS2040FL-AU_R1_000A1; SOD-123FL
D2: Red; D_0603_1608Metric
D3: Orange; D_0603_1608Metric
D4: Yellow; D_0603_1608Metric
D5: APTF1616LSEEZGKQBKC
D6, D7: SMLEN3WBC8W1; D_0603_1608Metric
FB1: 470; L_0603_1608Metric
J1: ILG2; ILG_01x02
J2: PA3; PA_01x03
J3: FFC4; Molex_200528-0040_1x04-1MP_P1.00mm_Horizontal
J4: FFC7; WürthElektronik_687112183722_01x12_P0.5mm
J5, J6: PA2; PA_01x02
Q1: CXDM4060P; SOT-89
R1, R5, R6, R7, R8, R9: 10k; R_0603_1608Metric
R2: 2k; D_0603_1608Metric
R3: 680; R_0603_1608Metric
R4: 270; R_0603_1608Metric
R10, R11: 16k; R_0603_1608Metric
R12, R13: 470; R_0603_1608Metric
R14, R15: 50k; R_0603_1608Metric
R16, R17, R19, R20: 1.2k; R_0603_1608Metric
R18: 1.5k; R_0603_1608Metric
RN1: 10k; SOIC-8_3.9x4.9mm_P1.27mm
SW1: SW_DPDT_x2; SSSS810701
SW2: 220AMB16R
SW3, SW4, SW5: SKRPABE010
U1: AZ1117R-5.0TRE1; SOT-89-3
U2: AZ1117IH-3.3TRG1; SOT-223-3_TabPin2
U3, U4: DRV8874; TSSOP_16-Pin

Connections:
+3V3: C4.1, J2.2, R4.1, R5.1, R6.1, R7.1, R8.1, R9.1, R10.1, R11.1, RN1.5, RN1.6, RN1.7, RN1.8, U2.2
+5V: C2.1, C3.1, D5.1, J2.1, R3.1, R12.1, R13.1, U1.2, U2.3
+BATT: C5.1, C6.1, C14.1, C15.1, C16.1, C17.1, C18.1, C19.1, D1.2, Q1.2, R2.1, U3.11, U4.11
/DRV1_EN: J3.1, U3.1
/DRV1_PN: J3.2, U3.2
/DRV2_EN: J3.4, U4.1
/DRV2_PN: J3.3, U4.2
/Rotary1: C7.1, J4.9, RN1.1, SW2.1
/Rotary2: C9.1, J4.7, RN1.3, SW2.2
/Rotary4: C10.1, J4.6, RN1.4, SW2.4
/Rotary8: C8.1, J4.8, RN1.2, SW2.8
/SW1: C13.1, J4.10, R7.2, SW5.1
/SW2: C12.1, J4.11, R6.2, SW4.1
/SW3: C11.1, J4.12, R5.2, SW3.1
GND: C1.2, C2.2, C3.2, C4.2, C5.2, C6.2, C7.2, C8.2, C9.2, C10.2, C11.2, C12.2, C13.2, C14.2, C15.2, C16.2, C17.2, D2.1, D3.1, D4.1, J1.1, J2.3, J3.MP, J4.MP, R14.2, R15.2, R16.2, R17.2, SW1.1, SW1.2, SW1.MP, SW2.C, SW3.2, SW4.2, SW5.2, U1.1, U2.1, U3.7, U3.9, U3.15, U3.16, U3.ThermalPad, U4.7, U4.9, U4.15, U4.16, U4.ThermalPad
unnamed: C1.1, FB1.1, U1.3
unnamed: C18.2, U3.12
unnamed: C19.2, U4.12
unnamed: C20.1, U3.13
unnamed: C20.2, U3.14
unnamed: C21.1, U4.13
unnamed: C21.2, U4.14
unnamed: D1.1, FB1.2
unnamed: D2.2, R2.2
unnamed: D3.2, R3.2
unnamed: D4.2, R4.2
unnamed: D5.2, R18.1
unnamed: D5.3, R19.1
unnamed: D5.4, R20.1
unnamed: D6.1, J4.2
unnamed: D6.2, R12.2
unnamed: D7.1, J4.1
unnamed: D7.2, R13.2
unnamed: J1.2, Q1.3, R1.1
unnamed: J4.3, R20.2
unnamed: J4.4, R19.2
unnamed: J4.5, R18.2
unnamed: J5.1, U3.8
unnamed: J5.2, U3.10
unnamed: J6.1, U4.8
unnamed: J6.2, U4.10
unnamed: Q1.1, R1.2, SW1.3
unnamed: R8.2, U3.3, U3.4
unnamed: R9.2, U4.3, U4.4
unnamed: R10.2, R14.1, U3.5
unnamed: R11.2, R15.1, U4.5
unnamed: R16.1, U3.6
unnamed: R17.1, U4.6

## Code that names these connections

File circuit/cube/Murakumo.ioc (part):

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Mcu.Name=STM32F405RGTx
Mcu.Package=LQFP64
Mcu.UserName=STM32F405RGTx
PA0-WKUP.Signal=ADCx_IN0
PA1.Signal=ADCx_IN1
PA10.Signal=GPIO_Output
PA11.Signal=GPIO_Output
PA12.Signal=GPIO_Output
PA13.Mode=Trace_Asynchronous_SW
PA13.Signal=SYS_JTMS-SWDIO
PA14.Mode=Trace_Asynchronous_SW
PA14.Signal=SYS_JTCK-SWCLK
PA15.GPIOParameters=GPIO_Label
PA15.GPIO_Label=Buzzer
PA15.Signal=S_TIM2_CH1_ETR
PA2.Signal=ADCx_IN2
PA3.Signal=ADCx_IN3
PA4.Signal=ADCx_IN4
PA5.Signal=ADCx_IN5
PA6.Signal=ADCx_IN6
PA7.Signal=ADCx_IN7
PA8.GPIOParameters=GPIO_Label
PA8.GPIO_Label=Encorder1_A
PA8.Signal=S_TIM1_CH1
PA9.GPIOParameters=GPIO_Label
PA9.GPIO_Label=Encorder1_B
PA9.Signal=S_TIM1_CH2
PB0.Signal=ADCx_IN8
PB1.Signal=ADCx_IN9
PB10.GPIOParameters=GPIO_Label
PB10.GPIO_Label=ICM_SCLK
PB10.Mode=Full_Duplex_Master
PB10.Signal=SPI2_SCK
PB11.GPIOParameters=GPIO_Label
PB11.GPIO_Label=SubSens2
PB11.Signal=GPIO_Input
PB12.GPIOParameters=GPIO_Label
PB12.GPIO_Label=ICM_nCS
PB12.Signal=GPIO_Output
PB13.GPIOParameters=GPIO_Label
PB13.GPIO_Label=LED_Red
PB13.Signal=GPIO_Input
PB14.GPIOParameters=GPIO_Label
PB14.GPIO_Label=ICM_MISO
PB14.Mode=Full_Duplex_Master
PB14.Signal=SPI2_MISO
PB15.GPIOParameters=GPIO_Label
PB15.GPIO_Label=ICM_MOSI
PB15.Mode=Full_Duplex_Master
PB15.Signal=SPI2_MOSI
PB2.GPIOParameters=GPIO_Label
PB2.GPIO_Label=SubSens1
PB2.Signal=GPIO_Input
PB3.Mode=Trace_Asynchronous_SW
PB3.Signal=SYS_JTDO-SWO
PB4.GPIOParameters=GPIO_Label
PB4.GPIO_Label=Encorder2_A
PB4.Signal=S_TIM3_CH1
PB5.GPIOParameters=GPIO_Label
PB5.GPIO_Label=Encorder2_B
PB5.Signal=S_TIM3_CH2
PB6.GPIOParameters=GPIO_Label
PB6.GPIO_Label=DRV1_EN
PB6.Signal=S_TIM4_CH1
PB7.GPIOParameters=GPIO_Label
PB7.GPIO_Label=DRV2_EN
PB7.Signal=S_TIM4_CH2
PB8.Mode=I2C
PB8.Signal=I2C1_SCL
PB9.Mode=I2C
PB9.Signal=I2C1_SDA
PC0.Signal=ADCx_IN10
PC1.Signal=ADCx_IN11
PC10.Signal=GPIO_Output
PC11.Signal=GPIO_Output
PC12.Signal=GPIO_Output
PC13-ANTI_TAMP.GPIOParameters=GPIO_Label
PC13-ANTI_TAMP.GPIO_Label=DRV2_PN
PC13-ANTI_TAMP.Signal=GPIO_Output
PC14-OSC32_IN.Signal=GPIO_Output
PC15-OSC32_OUT.Signal=GPIO_Output
PC2.Signal=ADCx_IN12
PC3.Signal=ADCx_IN13
PC4.Signal=ADCx_IN14
PC5.Signal=ADCx_IN15
PC6.Mode=Asynchronous
PC6.Signal=USART6_TX
PC7.Mode=Asynchronous
PC7.Signal=USART6_RX
PC8.Signal=GPIO_Output
PC9.Signal=GPIO_Output
PD2.GPIOParameters=GPIO_Label
PD2.GPIO_Label=DRV1_PN
PD2.Signal=GPIO_Output
PH0-OSC_IN.Signal=RCC_OSC_IN
PH1-OSC_OUT.GPIOParameters=GPIO_Label
PH1-OSC_OUT.GPIO_Label=SW3
PH1-OSC_OUT.Signal=GPIO_Input
RCC.HSE_VALUE=25000000
RCC.SYSCLKFreq_VALUE=16000000
board=custom

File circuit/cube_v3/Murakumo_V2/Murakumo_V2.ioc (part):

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Mcu.Name=STM32F405RGTx
Mcu.Package=LQFP64
Mcu.UserName=STM32F405RGTx
PA0-WKUP.Signal=ADCx_IN0
PA10.GPIOParameters=GPIO_Label
PA10.GPIO_Label=LED_G
PA10.Signal=GPIO_Output
PA11.GPIOParameters=GPIO_Label
PA11.GPIO_Label=LED_R
PA11.Signal=GPIO_Output
PA12.GPIOParameters=GPIO_Label
PA12.GPIO_Label=Rotary4
PA12.Signal=GPIO_Input
PA13.Mode=Trace_Asynchronous_SW
PA13.Signal=SYS_JTMS-SWDIO
PA14.Mode=Trace_Asynchronous_SW
PA14.Signal=SYS_JTCK-SWCLK
PA15.GPIOParameters=GPIO_Label
PA15.GPIO_Label=Buzzer
PA15.Signal=S_TIM2_CH1_ETR
PB11.GPIOParameters=GPIO_Label
PB11.GPIO_Label=SubSens2
PB11.Signal=GPIO_Input
PB13.GPIOParameters=GPIO_Label
PB13.GPIO_Label=LED_RED
PB13.Signal=GPIO_Output
PB2.GPIOParameters=GPIO_Label
PB2.GPIO_Label=SubSens1
PB2.Signal=GPIO_Input
PB3.Mode=Trace_Asynchronous_SW
PB3.Signal=SYS_JTDO-SWO
PB6.GPIOParameters=GPIO_Label
PB6.GPIO_Label=DRV1_EN
PB6.Signal=S_TIM4_CH1
PB7.GPIOParameters=GPIO_Label
PB7.GPIO_Label=DRV2_EN
PB7.Signal=S_TIM4_CH2
PC10.GPIOParameters=GPIO_Label
PC10.GPIO_Label=Rotary2
PC10.Signal=GPIO_Input
PC11.GPIOParameters=GPIO_Label
PC11.GPIO_Label=Rotary8
PC11.Signal=GPIO_Input
PC12.GPIOParameters=GPIO_Label
PC12.GPIO_Label=Rotary1
PC12.Signal=GPIO_Input
PC13-ANTI_TAMP.GPIOParameters=GPIO_Label
PC13-ANTI_TAMP.GPIO_Label=DRV2_PH
PC13-ANTI_TAMP.Signal=GPIO_Output
PC14-OSC32_IN.GPIOParameters=GPIO_Label
PC14-OSC32_IN.GPIO_Label=SW1
PC14-OSC32_IN.Signal=GPIO_Input
PC6.Mode=Asynchronous
PC6.Signal=USART6_TX
PC7.Mode=Asynchronous
PC7.Signal=USART6_RX
PC8.GPIOParameters=GPIO_Label
PC8.GPIO_Label=LED_White
PC8.Signal=GPIO_Output
PC9.GPIOParameters=GPIO_Label
PC9.GPIO_Label=LED_B
PC9.Signal=GPIO_Output
PD2.GPIOParameters=GPIO_Label
PD2.GPIO_Label=DRV1_PH
PD2.Signal=GPIO_Output
RCC.HSE_VALUE=16000000
RCC.SYSCLKFreq_VALUE=168000000
RCC.SYSCLKSource=RCC_SYSCLKSOURCE_PLLCLK
board=custom

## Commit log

2021-09-07 Excel の追加
2021-09-15 Excel を編集
2021-09-21 Odakun Version
2021-09-21 DCX の CAD データの追加
2021-09-22 タイヤのアセンブリを作成中
2021-09-24 excel データの修正
2021-09-25 タイヤ一つ分完成
2021-10-02 Excel のギアシートに伝達効率を考慮した Version4 を追加した。
2021-10-06 CFRP 土台の作成中
2021-10-12 天板を追加。あとはセンサバーをつければヨシッ！
2021-10-12 センサバーどうしよう...
2021-10-13 センサバーの試行錯誤
2021-10-17 センサ基板形状の決定
2021-10-25 点検してもらった。正直天板そんなに広くとる必要ないし、センサバーも二階から引き延ばさずに一階とつなげれば良いのでは？
2021-10-28 hogehoge
2021-11-12 回路図フォルダを作成。
2021-11-16 add README.md
2021-11-24 レギュレータ選定の Excel を追加。
2021-12-27 サイドセンサを角度可変にした
2022-01-13 hoge
2022-01-15 DRV8874
2022-01-16 なぜかファイルが開けなくなったので作り直す。（元々そんなに進んでなかったし...）
2022-01-24 Create queue
2022-01-27 機体全体的に無駄な部分を減らした。
2022-01-27 オシレータ増やした。モータドライバの信号を CPU で読めるようにした。nRST にプルアップ抵抗を接続。まだ CPU の正しいピンに正しい線をつなげることができていない。
2022-01-28 次はフットプリントの関連付け
2022-01-29 あとちょっとでフットプリントの関連付けが終わる
2022-01-30 回路図とフットプリントの関連付けが終わった
2022-01-30 基板毎の回路図を別のプログラムとして開けるようにした
2022-01-30 センサーバーの改良
2022-01-30 サイドセンサの改良とセンサーバーマウンタの厚みを減らした
2022-01-30 dxf ファイルの追加
2022-01-31 calclator.c
2022-01-31 サイドセンサのパターンは完成。メイン基板のフットプリント配置は完了。
2022-01-31 calcv2.cpp
2022-01-31 dxf ファイルのリビジョン
2022-01-31 150x50 のセンサーバーにした
2022-01-31 パーツ配置まではとりあえず終わらせた。後は配線すればいい。
2022-01-31 重心位置を考慮
2022-01-31 power 基板の肉抜きを無くした
2022-02-03 とりあえず完成
2022-02-04 あとはシルクを見やすい位置にもっていくだけ。
2022-02-04 これから gerber ファイルを吐き出して先輩たちに見てもらう
2022-02-04 Gerber データを出力した。これから先輩に添削してもらう。
2022-02-04 シルクの調整
2022-02-04 ファイル名の変更。シルクの調整。
2022-02-05 フットプリントの問題は解消
2022-02-05 後はガーバデータ出してロゴ刺すだけ
2022-02-06 export
2022-02-17 ホイールの改善とシャフトの編集
2022-03-02 タイヤをギアと一体化させた
2022-03-09 2hoge
2022-03-09 cube_v2 _v3 を消した
2022-03-11 でーきーなーいー
2022-03-11 取り消す前
2022-03-16 感光基板で作れるフロントセンサを作成中
2022-03-29 P 制御するプログラムを実装（まだ実機で実験してないけど...
2022-03-31 Excel ファイルの追加 センサ値を CSV で吐けるようにした
2022-04-08 センサの位置を計算して出してくれる Excel を作った。
2022-04-10 add analogcalctest
2022-04-10 式の修正
2022-04-12 はしるよ
2022-04-13 Wheel_v4 add
2022-04-28 testcommit
2022-04-28 さらにテスト
2022-04-28 さらにさらにテスト
2022-05-05 サイドセンサのプログラムの吟味
2022-05-19 一旦保存、何かあったらここに戻れ
2022-05-23 サイドセンサだけのプログラムを実行できるようにプリプロセッサを登録した。
2022-06-26 Encoder Rotary Switch
2022-06-27 analog の処理のあたりを改善
2022-06-28 ロータリスイッチを使ってモード変更のプログラムの書き途中
2022-06-30 ロータリスイッチのプログラムを実装する。何か問題が起きたらここに戻れ
2022-06-30 オペ完了
2022-06-30 ロータリスイッチを実装した状態で元の状態と同じ状態に戻れた
2022-07-01 Flash のプログラムを書こうと思ったけどやめた
2022-07-20 IMU のデータを取得できた！
2022-07-22 減速比を考え直して設計しなおした
2022-07-26 UART が使えなくなったぞ？？？
2022-08-05 FPU を有効化した
2022-08-05 ノムさんが9号館にいてくれたから...
2022-08-08 ライントレースしながらちゃんと目標速度が出せるようになった！
2022-08-08 交差でぶれないようにした。
2022-09-08 何かあったらここに戻れ
2022-09-08 PlayMode 追加、また、ゲイン値の与え方を修正、14 通りでゲインを試せるようにした。
2022-09-18 PID ゲインチューニング中
2022-09-18 大型アップデート前、戻るならここ。
2022-09-26 ボディファイルの可読化
2022-09-26 大型アップデート前、戻るならここ
2022-10-10 東日本大会に出ました
2022-10-10 何が変わった？？？
2022-10-10 細かいところちょっとだけ修正した
2022-10-22 ヘッダファイルを追加して可読性の高いプログラムに編集していく
2022-11-11 hoge2
2022-11-16 とりあえずコンパイルエラーが出ないところまでできたけど、なぜか動かん#
2022-11-16 バックアップ用のブランチ
2022-11-18 Analog の入力電圧がなんだか変
2022-11-18 ADC のソートを修正
2022-11-19 モータが動かない
2022-11-22 code ワークスペースの追加
2023-02-05 センサバーのデータが無くなってたから作り直した
